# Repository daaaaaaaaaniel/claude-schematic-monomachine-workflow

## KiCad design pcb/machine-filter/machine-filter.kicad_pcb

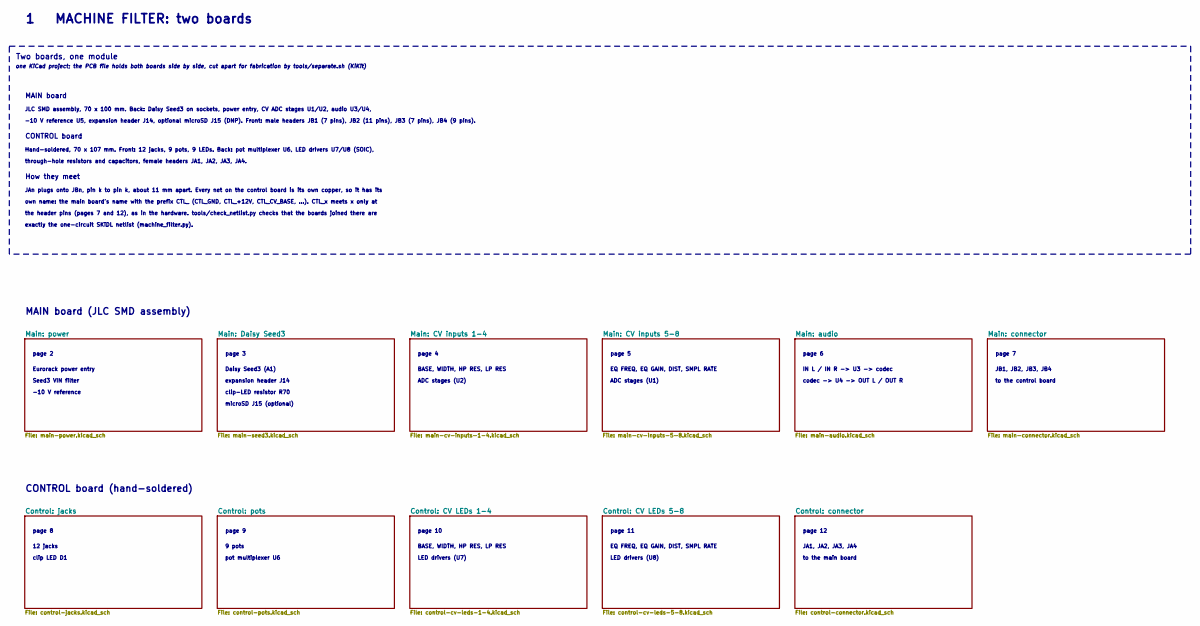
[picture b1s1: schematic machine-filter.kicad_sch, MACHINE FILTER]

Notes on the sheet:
Two boards, one module
one KiCad project; the PCB file holds both boards side by side, cut apart for fabrication by tools/separate.sh (KiKit)
MAIN board
JLC SMD assembly, 70 x 100 mm. Back: Daisy Seed3 on sockets, power entry, CV ADC stages U1/U2, audio U3/U4,
-10 V reference U5, expansion header J14, optional microSD J15 (DNP). Front: male headers JB1 (7 pins), JB2 (11 pins), JB3 (7 pins), JB4 (9 pins).
CONTROL board
Hand-soldered, 70 x 107 mm. Front: 12 jacks, 9 pots, 9 LEDs. Back: pot multiplexer U6, LED drivers U7/U8 (SOIC),
through-hole resistors and capacitors, female headers JA1, JA2, JA3, JA4.
How they meet
JAn plugs onto JBn, pin k to pin k, about 11 mm apart. Every net on the control board is its own copper, so it has its
own name: the main board's name with the prefix CTL_ (CTL_GND, CTL_+12V, CTL_CV_BASE, ...). CTL_x meets x only at
the header pins (pages 7 and 12), as in the hardware. tools/check_netlist.py checks that the boards joined there are
exactly the one-circuit SKiDL netlist (machine_filter.py).
MAIN board (JLC SMD assembly)
page 2
Eurorack power entry
Seed3 VIN filter
-10 V reference
page 3
Daisy Seed3 (A1)
expansion header J14
clip-LED resistor R70
microSD J15 (optional)
page 4
BASE, WIDTH, HP RES, LP RES
ADC stages (U2)
page 5
EQ FREQ, EQ GAIN, DIST, SMPL RATE
ADC stages (U1)
page 6
IN L / IN R -> U3 -> codec
codec -> U4 -> OUT L / OUT R
page 7
JB1, JB2, JB3, JB4
to the control board
CONTROL board (hand-soldered)
page 8
12 jacks
clip LED D1
page 9

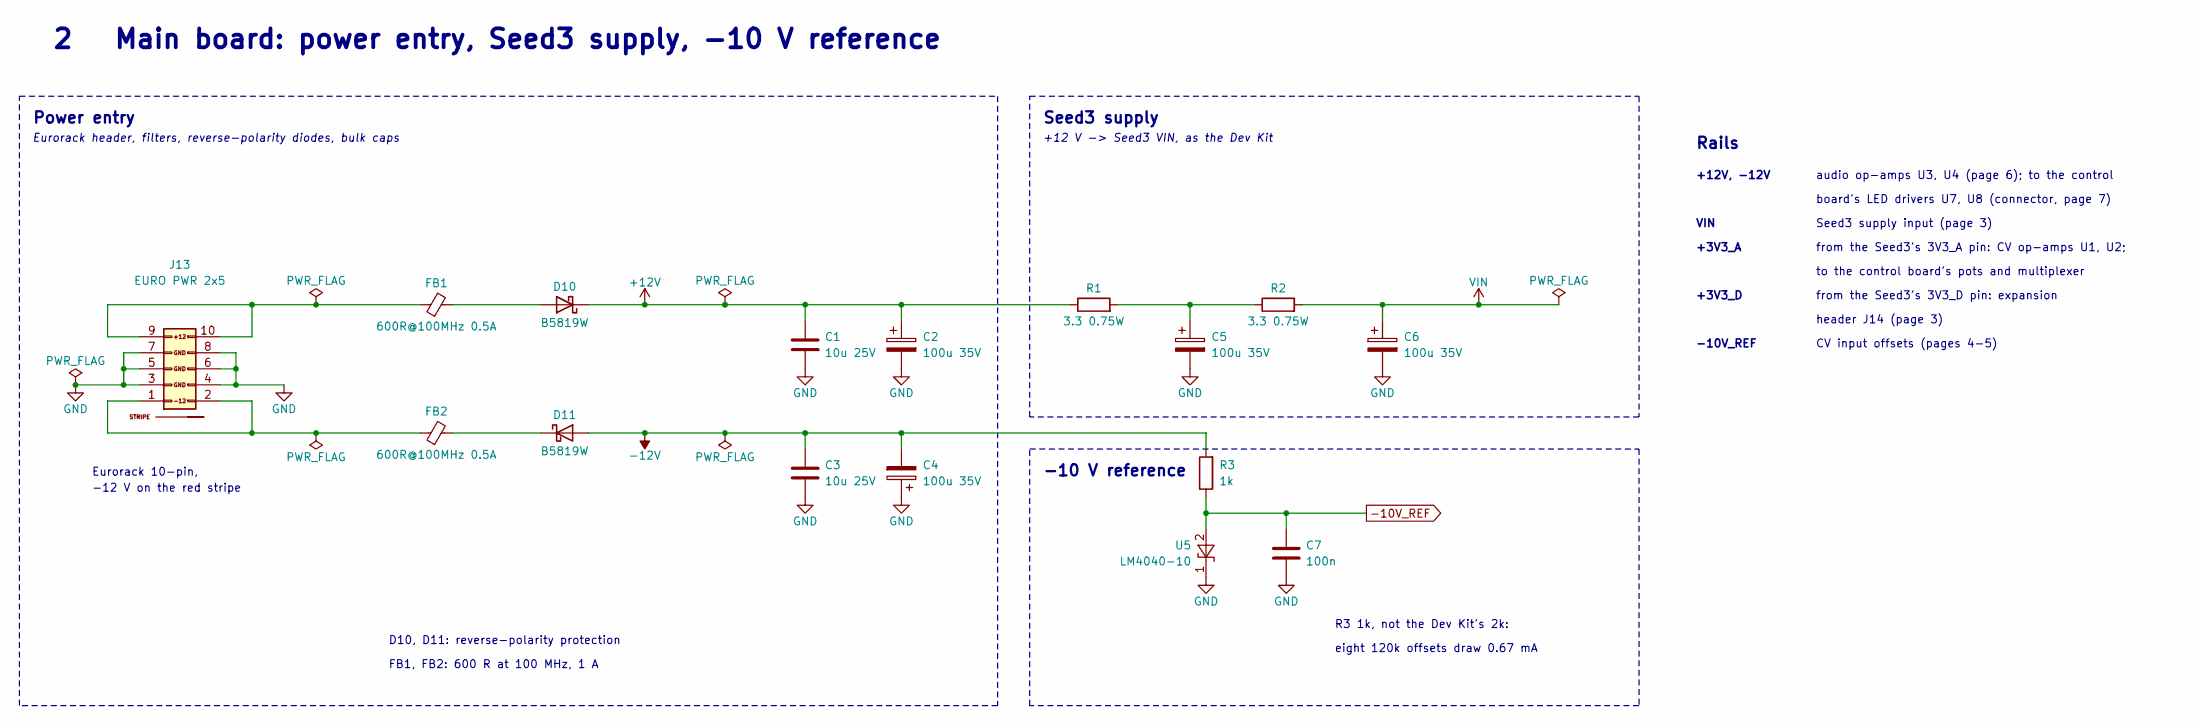
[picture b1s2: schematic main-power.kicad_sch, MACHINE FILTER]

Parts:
C1, C3: 10u 25V; C_0805; MPN CL21A106KAYNNNE; LCSC C15850
C2, C4, C5, C6: 100u 35V; CP_Elec_6.3x7.7; MPN RVT1V101M0607; LCSC C72478
C7: 100n; C_0603; MPN CC0603KRX7R9BB104; LCSC C14663
D10, D11: B5819W; D_SOD-123; MPN B5819W SL; LCSC C8598
FB1, FB2: 600R@100MHz 0.5A; R_0805_2012Metric; MPN GZ2012D601TF; LCSC C1017
J13: EURO PWR 2x5; Pins_2x05_2.54mm_TH_EurorackPower_Shrouded; MPN 2x5 2.54 mm shrouded box header
R1, R2: 3.3 0.75W; R_1206_3216Metric; MPN SG73P2BTTD3R30F; LCSC C2577888
R3: 1k; R_0603; MPN 0603WAF1001T5E; LCSC C21190
U5: LM4040-10; SOT-23; MPN LM4040C10IDBZR; LCSC C201738

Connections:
+12V: C1.1, C2.1, D10.1 (K), R1.1; also elsewhere on the board
-10V_REF: C7.1, R3.1, U5.2 (A); also elsewhere on the board
-12V: C3.2, C4.2, D11.2 (A), R3.2; also elsewhere on the board
GND: C1.2, C2.2, C3.1, C4.1, C5.2, C6.2, C7.2, J13.3 (GND), J13.4 (GND), J13.5 (GND), J13.6 (GND), J13.7 (GND), J13.8 (GND), U5.1 (K); also elsewhere on the board
unnamed: C5.1, R1.2, R2.1
unnamed: D10.2 (A), FB1.2
unnamed: D11.1 (K), FB2.2
unnamed: FB1.1, J13.9 (+12V), J13.10 (+12V)
unnamed: FB2.1, J13.1 (-12V), J13.2 (-12V)
VIN: C6.1, R2.2; also elsewhere on the board

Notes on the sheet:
Power entry
Eurorack header, filters, reverse-polarity diodes, bulk caps
Eurorack 10-pin,
-12 V on the red stripe
Seed3 supply
+12 V -> Seed3 VIN, as the Dev Kit
D10, D11: reverse-polarity protection
FB1, FB2: 600 R at 100 MHz, 1 A
-10 V reference
R3 1k, not the Dev Kit's 2k:
eight 120k offsets draw 0.67 mA
Rails
+12V, -12V
audio op-amps U3, U4 (page 6); to the control
board's LED drivers U7, U8 (connector, page 7)
VIN
Seed3 supply input (page 3)
+3V3_A
from the Seed3's 3V3_A pin: CV op-amps U1, U2;
to the control board's pots and multiplexer
+3V3_D
from the Seed3's 3V3_D pin: expansion
header J14 (page 3)
-10V_REF
CV input offsets (pages 4-5)
2 Main board: power entry, Seed3 supply, -10 V reference

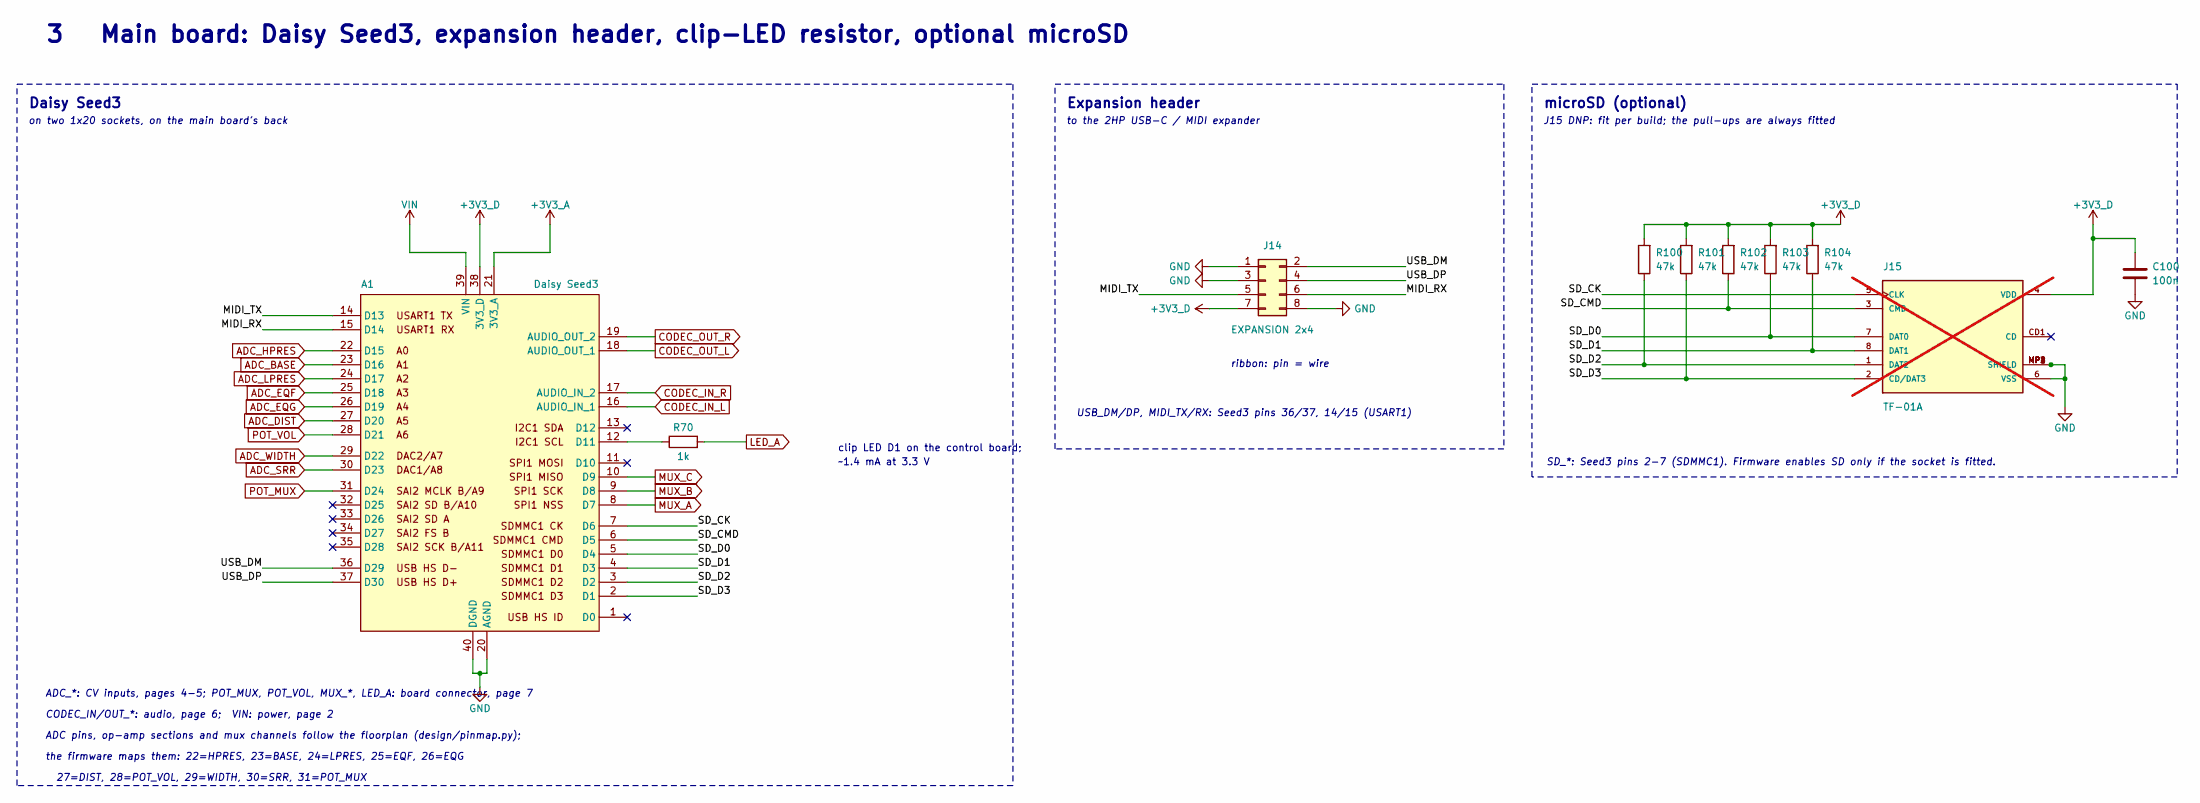
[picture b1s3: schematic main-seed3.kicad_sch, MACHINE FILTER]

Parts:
A1: Daisy Seed3; Daisy_Seed_ES_Sockets; MPN Electrosmith Daisy Seed3 on 2x 1x20 2.5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
C100: 100n; C_0603; MPN CC0603KRX7R9BB104; LCSC C14663
J14: EXPANSION 2x4; Pins_2x04_2.54mm_TH; MPN 2x4 2.54 mm pin header, unshrouded (d)
J15: TF-01A; MPN HRO TF-01A microSD socket, push-push (o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; LCSC C91145; not fitted
R70: 1k; R_0603; MPN 0603WAF1001T5E; LCSC C21190
R100, R101, R102, R103, R104: 47k; R_0603; MPN 0603WAF4702T5E; LCSC C25819

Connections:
+3V3_A: A1.21 (3V3_A); also elsewhere on the board
+3V3_D: A1.38 (3V3_D), C100.1, J14.7, J15.4 (VDD), R100.2, R101.2, R102.2, R103.2, R104.2
/Main: Daisy Seed3/MIDI_RX: A1.15 (D14), J14.6
/Main: Daisy Seed3/MIDI_TX: A1.14 (D13), J14.5
/Main: Daisy Seed3/SD_CK: A1.7 (D6), J15.5 (CLK)
/Main: Daisy Seed3/SD_CMD: A1.6 (D5), J15.3 (CMD), R102.1
/Main: Daisy Seed3/SD_D0: A1.5 (D4), J15.7 (DAT0), R103.1
/Main: Daisy Seed3/SD_D1: A1.4 (D3), J15.8 (DAT1), R104.1
/Main: Daisy Seed3/SD_D2: A1.3 (D2), J15.1 (DAT2), R100.1
/Main: Daisy Seed3/SD_D3: A1.2 (D1), J15.2 (CD/DAT3), R101.1
/Main: Daisy Seed3/USB_DM: A1.36 (D29), J14.2
/Main: Daisy Seed3/USB_DP: A1.37 (D30), J14.4
ADC_BASE: A1.23 (D16); also elsewhere on the board
ADC_DIST: A1.27 (D20); also elsewhere on the board
ADC_EQF: A1.25 (D18); also elsewhere on the board
ADC_EQG: A1.26 (D19); also elsewhere on the board
ADC_HPRES: A1.22 (D15); also elsewhere on the board
ADC_LPRES: A1.24 (D17); also elsewhere on the board
ADC_SRR: A1.30 (D23); also elsewhere on the board
ADC_WIDTH: A1.29 (D22); also elsewhere on the board
CODEC_IN_L: A1.16 (AUDIO_IN_1); also elsewhere on the board
CODEC_IN_R: A1.17 (AUDIO_IN_2); also elsewhere on the board
CODEC_OUT_L: A1.18 (AUDIO_OUT_1); also elsewhere on the board
CODEC_OUT_R: A1.19 (AUDIO_OUT_2); also elsewhere on the board
GND: A1.20 (AGND), A1.40 (DGND), C100.2, J14.1, J14.3, J14.8, J15.6 (VSS), J15.MP1 (SHIELD), J15.MP2 (SHIELD), J15.MP3 (SHIELD), J15.MP4 (SHIELD); also elsewhere on the board
LED_A: R70.2; also elsewhere on the board
MUX_A: A1.8 (D7); also elsewhere on the board
MUX_B: A1.9 (D8); also elsewhere on the board
MUX_C: A1.10 (D9); also elsewhere on the board
unnamed: A1.12 (D11), R70.1
POT_MUX: A1.31 (D24); also elsewhere on the board
POT_VOL: A1.28 (D21); also elsewhere on the board
VIN: A1.39 (VIN); also elsewhere on the board

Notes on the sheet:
Daisy Seed3
on two 1x20 sockets, on the main board's back
clip LED D1 on the control board;
~1.4 mA at 3.3 V
ADC_*: CV inputs, pages 4-5; POT_MUX, POT_VOL, MUX_*, LED_A: board connector, page 7
CODEC_IN/OUT_*: audio, page 6; VIN: power, page 2
ADC pins, op-amp sections and mux channels follow the floorplan (design/pinmap.py);
the firmware maps them: 22=HPRES, 23=BASE, 24=LPRES, 25=EQF, 26=EQG
27=DIST, 28=POT_VOL, 29=WIDTH, 30=SRR, 31=POT_MUX
Expansion header
to the 2HP USB-C / MIDI expander
ribbon: pin = wire
USB_DM/DP, MIDI_TX/RX: Seed3 pins 36/37, 14/15 (USART1)
microSD (optional)
J15 DNP: fit per build; the pull-ups are always fitted
SD_*: Seed3 pins 2-7 (SDMMC1). Firmware enables SD only if the socket is fitted.
3 Main board: Daisy Seed3, expansion header, clip-LED resistor, optional microSD

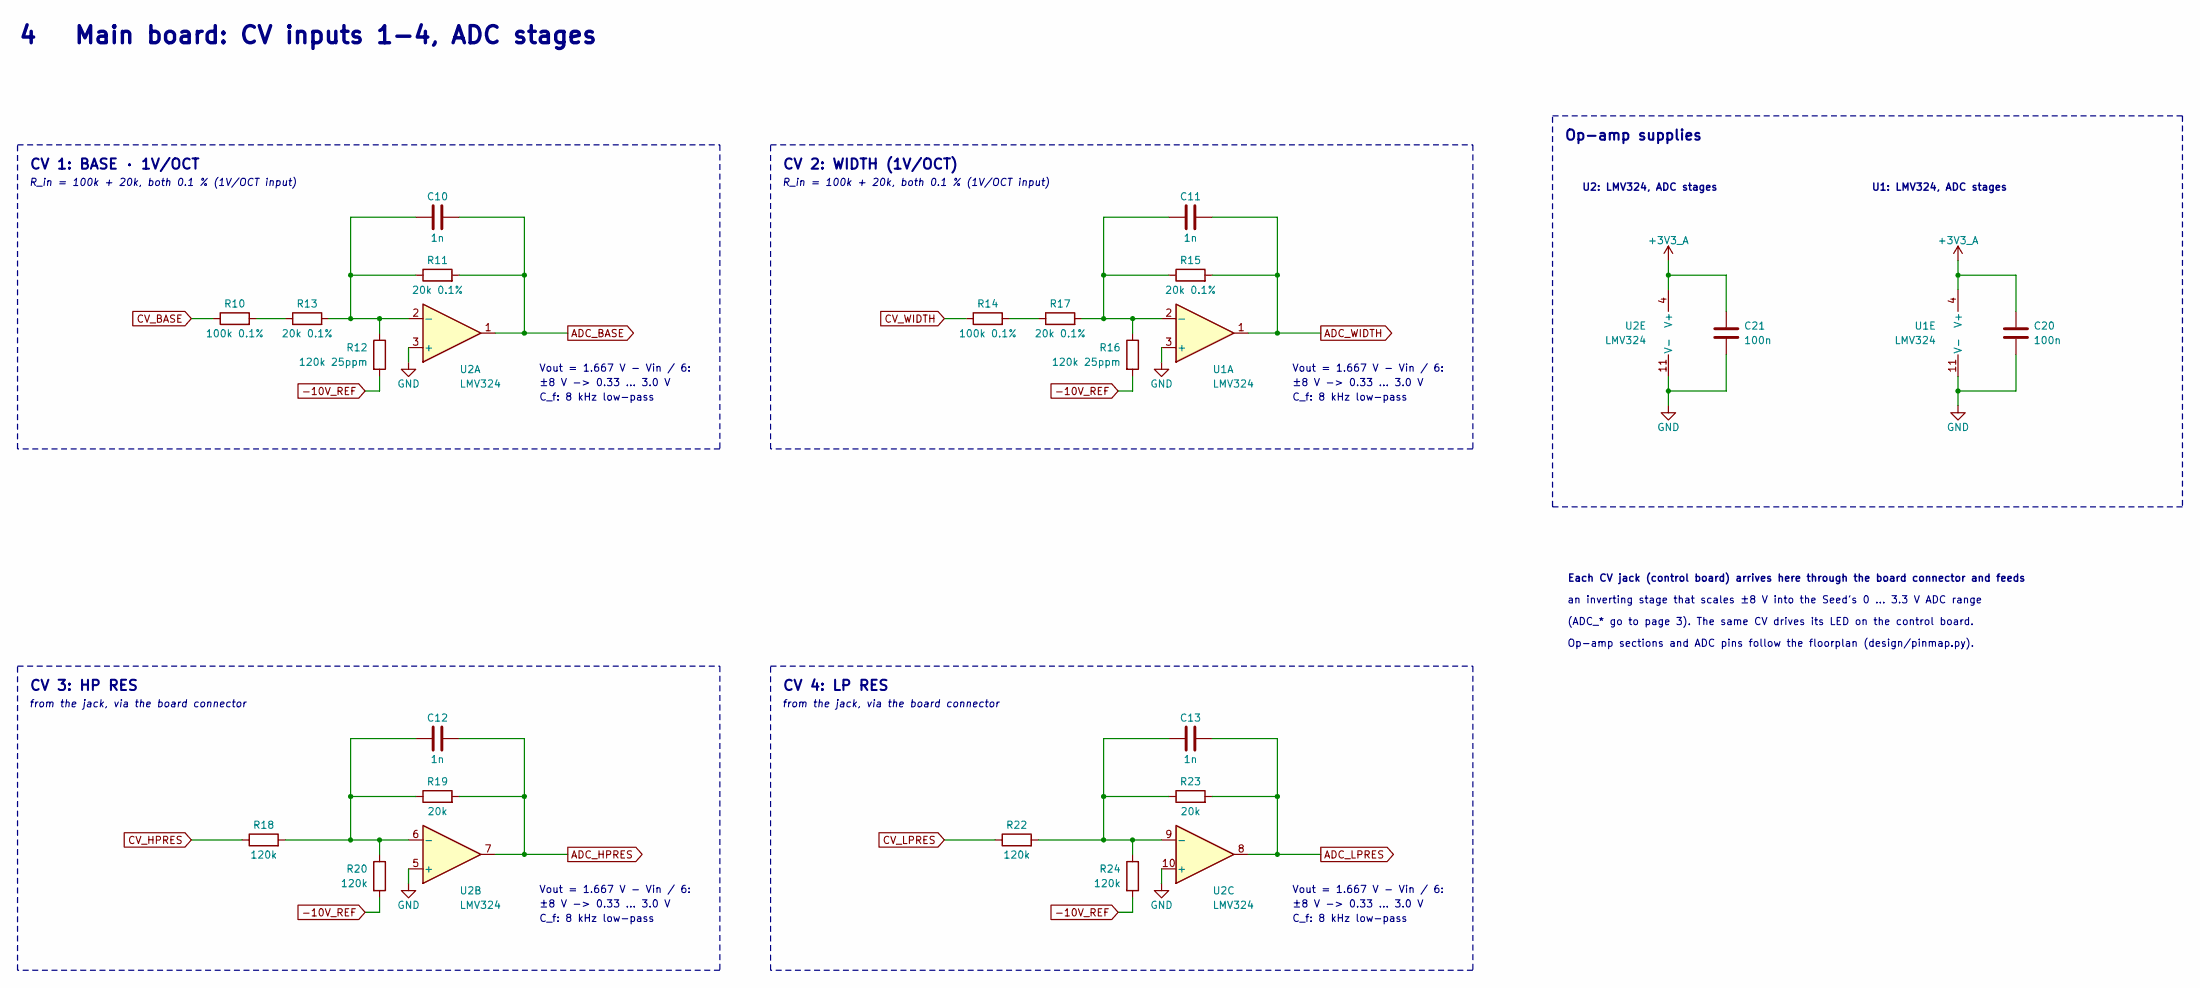
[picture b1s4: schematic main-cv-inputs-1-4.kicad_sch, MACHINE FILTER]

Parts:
C10, C11, C12, C13: 1n; C_0603; MPN CL10B102KB8NNNC; LCSC C1588
C20, C21: 100n; C_0603; MPN CC0603KRX7R9BB104; LCSC C14663
R10, R14: 100k 0.1%; R_0603; MPN RT0603BRD07100KL; LCSC C122538
R11, R13, R15, R17: 20k 0.1%; R_0603; MPN RT0603BRD0720KL; LCSC C723637
R12, R16: 120k 25ppm; R_0603; MPN RT0603DRD07120KL; LCSC C862537
R18, R20, R22, R24: 120k; R_0603; MPN 0603WAF1203T5E; LCSC C25808
R19, R23: 20k; R_0603; MPN 0603WAF2002T5E; LCSC C4184
U1, U2: LMV324; SOIC-14_3.9x8.65mm_Pitch1.27mm; MPN LMV324IDR; LCSC C7974

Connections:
+3V3_A: C20.1, C21.1, U1.4 (V+), U2.4 (V+); also elsewhere on the board
-10V_REF: R12.2, R16.2, R20.2, R24.2; also elsewhere on the board
ADC_BASE: C10.2, R11.2, U2.1; also elsewhere on the board
ADC_HPRES: C12.2, R19.2, U2.7; also elsewhere on the board
ADC_LPRES: C13.2, R23.2, U2.8; also elsewhere on the board
ADC_WIDTH: C11.2, R15.2, U1.1; also elsewhere on the board
CV_BASE: R10.1; also elsewhere on the board
CV_HPRES: R18.1; also elsewhere on the board
CV_LPRES: R22.1; also elsewhere on the board
CV_WIDTH: R14.1; also elsewhere on the board
GND: C20.2, C21.2, U1.3 (+), U1.11 (V-), U2.3 (+), U2.5 (+), U2.10 (+), U2.11 (V-); also elsewhere on the board
unnamed: R10.2, R13.1
unnamed: R14.2, R17.1
unnamed: C11.1, R15.1, R16.1, R17.2, U1.2 (-)
unnamed: C10.1, R11.1, R12.1, R13.2, U2.2 (-)
unnamed: C12.1, R18.2, R19.1, R20.1, U2.6 (-)
unnamed: C13.1, R22.2, R23.1, R24.1, U2.9 (-)

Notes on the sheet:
CV 1: BASE · 1V/OCT
R_in = 100k + 20k, both 0.1 % (1V/OCT input)
Vout = 1.667 V - Vin / 6:
±8 V -> 0.33 ... 3.0 V
C_f: 8 kHz low-pass
CV 2: WIDTH (1V/OCT)
CV 3: HP RES
from the jack, via the board connector
CV 4: LP RES
Op-amp supplies
U2: LMV324, ADC stages
U1: LMV324, ADC stages
Each CV jack (control board) arrives here through the board connector and feeds
an inverting stage that scales ±8 V into the Seed's 0 ... 3.3 V ADC range
(ADC_* go to page 3). The same CV drives its LED on the control board.
Op-amp sections and ADC pins follow the floorplan (design/pinmap.py).
4 Main board: CV inputs 1-4, ADC stages

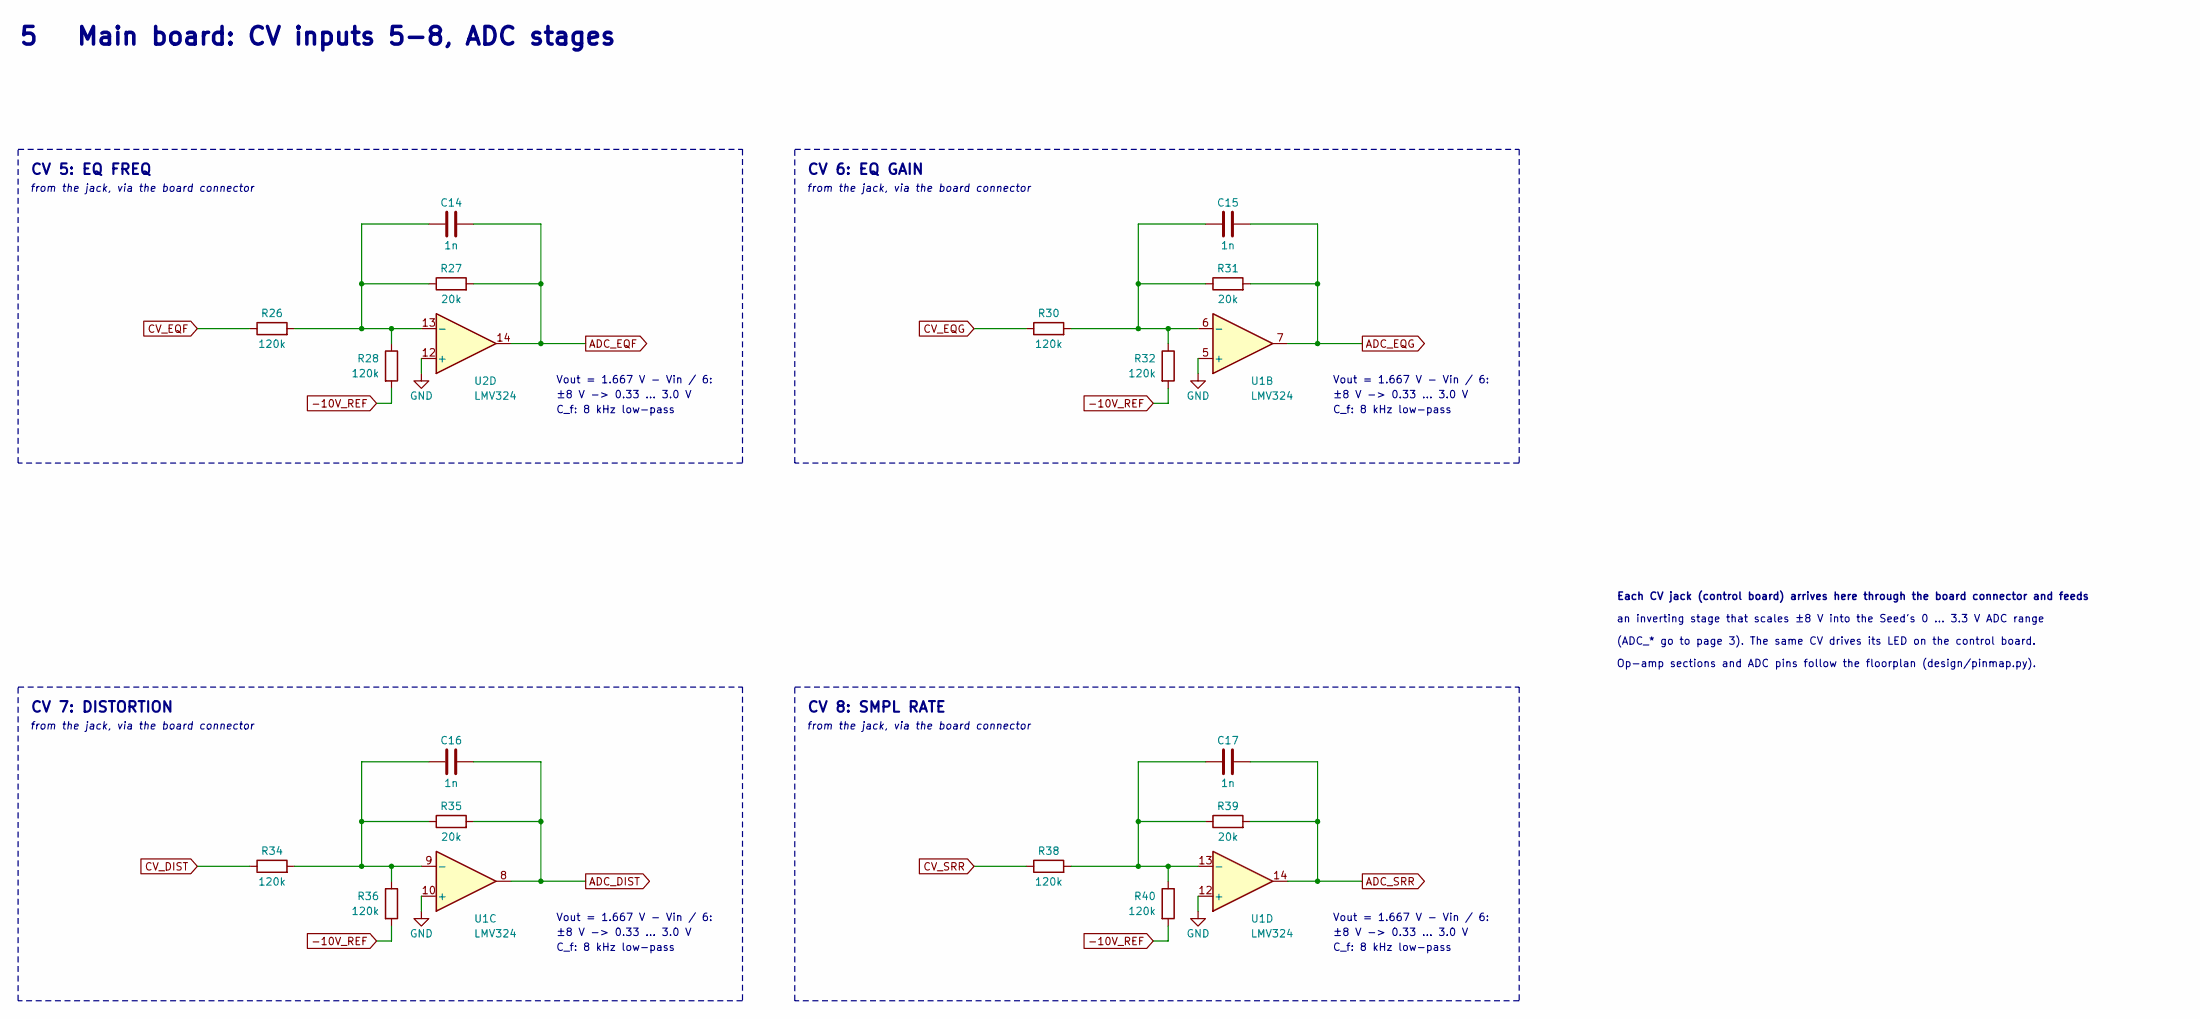
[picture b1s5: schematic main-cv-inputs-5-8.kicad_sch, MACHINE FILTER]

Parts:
C14, C15, C16, C17: 1n; C_0603; MPN CL10B102KB8NNNC; LCSC C1588
R26, R28, R30, R32, R34, R36, R38, R40: 120k; R_0603; MPN 0603WAF1203T5E; LCSC C25808
R27, R31, R35, R39: 20k; R_0603; MPN 0603WAF2002T5E; LCSC C4184
U1, U2: LMV324; SOIC-14_3.9x8.65mm_Pitch1.27mm; MPN LMV324IDR; LCSC C7974

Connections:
-10V_REF: R28.2, R32.2, R36.2, R40.2; also elsewhere on the board
ADC_DIST: C16.2, R35.2, U1.8; also elsewhere on the board
ADC_EQF: C14.2, R27.2, U2.14; also elsewhere on the board
ADC_EQG: C15.2, R31.2, U1.7; also elsewhere on the board
ADC_SRR: C17.2, R39.2, U1.14; also elsewhere on the board
CV_DIST: R34.1; also elsewhere on the board
CV_EQF: R26.1; also elsewhere on the board
CV_EQG: R30.1; also elsewhere on the board
CV_SRR: R38.1; also elsewhere on the board
GND: U1.5 (+), U1.10 (+), U1.12 (+), U2.12 (+); also elsewhere on the board
unnamed: C15.1, R30.2, R31.1, R32.1, U1.6 (-)
unnamed: C16.1, R34.2, R35.1, R36.1, U1.9 (-)
unnamed: C17.1, R38.2, R39.1, R40.1, U1.13 (-)
unnamed: C14.1, R26.2, R27.1, R28.1, U2.13 (-)

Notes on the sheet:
CV 5: EQ FREQ
from the jack, via the board connector
Vout = 1.667 V - Vin / 6:
±8 V -> 0.33 ... 3.0 V
C_f: 8 kHz low-pass
CV 6: EQ GAIN
CV 7: DISTORTION
CV 8: SMPL RATE
Each CV jack (control board) arrives here through the board connector and feeds
an inverting stage that scales ±8 V into the Seed's 0 ... 3.3 V ADC range
(ADC_* go to page 3). The same CV drives its LED on the control board.
Op-amp sections and ADC pins follow the floorplan (design/pinmap.py).
5 Main board: CV inputs 5-8, ADC stages

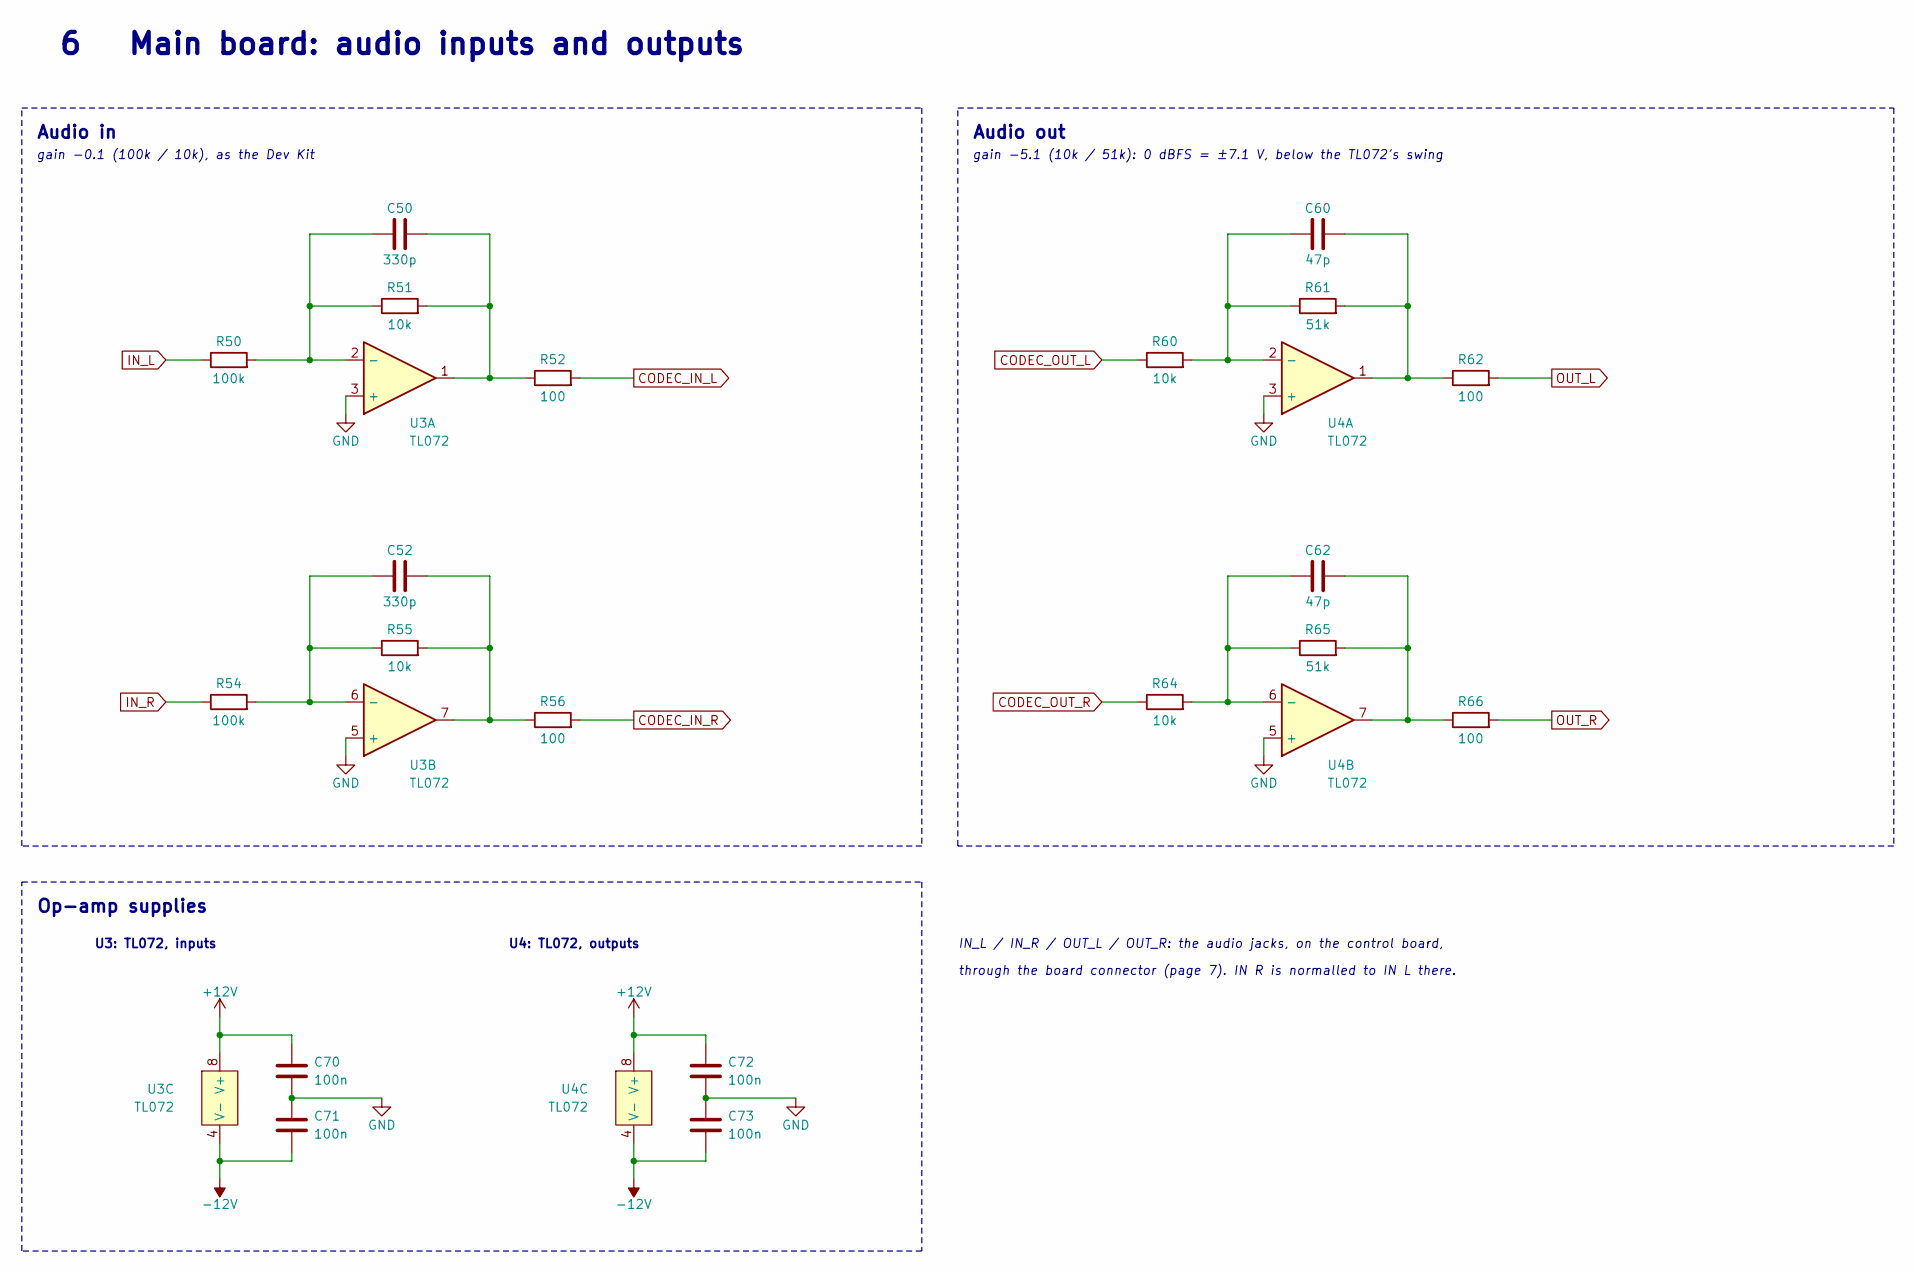
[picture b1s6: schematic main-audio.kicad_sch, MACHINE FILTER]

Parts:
C50, C52: 330p; C_0603; MPN CL10C331JB8NNNC; LCSC C1664
C60, C62: 47p; C_0603; MPN CL10C470JB8NNNC; LCSC C1671
C70, C71, C72, C73: 100n; C_0603; MPN CC0603KRX7R9BB104; LCSC C14663
R50, R54: 100k; R_0603; MPN 0603WAF1003T5E; LCSC C25803
R51, R55, R60, R64: 10k; R_0603; MPN 0603WAF1002T5E; LCSC C25804
R52, R56, R62, R66: 100; R_0603; MPN 0603WAF1000T5E; LCSC C22775
R61, R65: 51k; R_0603; MPN 0603WAF5102T5E; LCSC C23196
U3, U4: TL072; SOIC-8_3.9x4.9mm_Pitch1.27mm; MPN TL072CDT; LCSC C6961

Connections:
+12V: C70.1, C72.1, U3.8 (V+), U4.8 (V+); also elsewhere on the board
-12V: C71.2, C73.2, U3.4 (V-), U4.4 (V-); also elsewhere on the board
CODEC_IN_L: R52.2; also elsewhere on the board
CODEC_IN_R: R56.2; also elsewhere on the board
CODEC_OUT_L: R60.1; also elsewhere on the board
CODEC_OUT_R: R64.1; also elsewhere on the board
GND: C70.2, C71.1, C72.2, C73.1, U3.3 (+), U3.5 (+), U4.3 (+), U4.5 (+); also elsewhere on the board
IN_L: R50.1; also elsewhere on the board
IN_R: R54.1; also elsewhere on the board
unnamed: C50.2, R51.2, R52.1, U3.1
unnamed: C52.2, R55.2, R56.1, U3.7
unnamed: C60.2, R61.2, R62.1, U4.1
unnamed: C62.2, R65.2, R66.1, U4.7
unnamed: C50.1, R50.2, R51.1, U3.2 (-)
unnamed: C52.1, R54.2, R55.1, U3.6 (-)
unnamed: C60.1, R60.2, R61.1, U4.2 (-)
unnamed: C62.1, R64.2, R65.1, U4.6 (-)
OUT_L: R62.2; also elsewhere on the board
OUT_R: R66.2; also elsewhere on the board

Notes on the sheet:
Audio in
gain -0.1 (100k / 10k), as the Dev Kit
Audio out
gain -5.1 (10k / 51k): 0 dBFS = ±7.1 V, below the TL072's swing
Op-amp supplies
U3: TL072, inputs
U4: TL072, outputs
IN_L / IN_R / OUT_L / OUT_R: the audio jacks, on the control board,
through the board connector (page 7). IN R is normalled to IN L there.
6 Main board: audio inputs and outputs

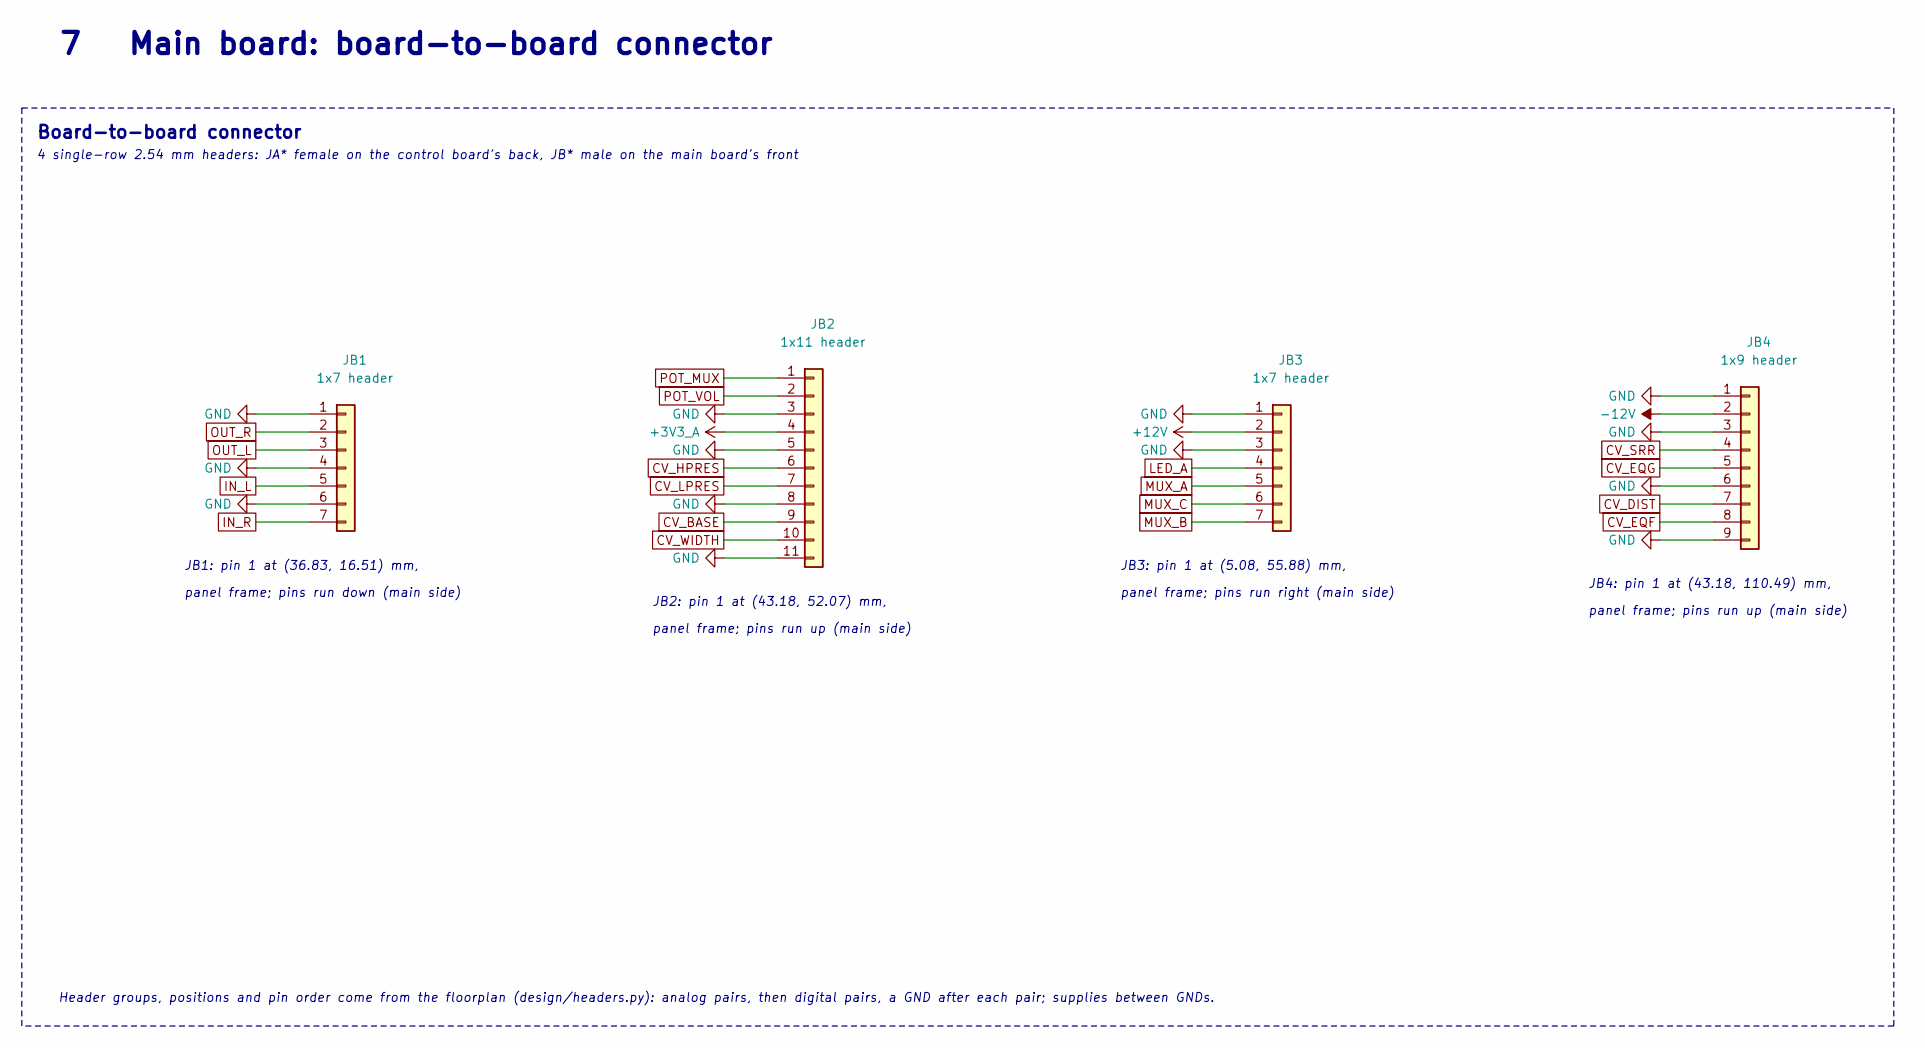
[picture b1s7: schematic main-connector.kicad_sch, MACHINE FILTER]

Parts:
JB1, JB3: 1x7 header; PinHeader_1x07_P2.54mm_Vertical; MPN 2.54 mm male pin header 1x7
JB2: 1x11 header; PinHeader_1x11_P2.54mm_Vertical; MPN 2.54 mm male pin header 1x11
JB4: 1x9 header; PinHeader_1x09_P2.54mm_Vertical; MPN 2.54 mm male pin header 1x9

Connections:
+3V3_A: JB2.4; also elsewhere on the board
+12V: JB3.2; also elsewhere on the board
-12V: JB4.2; also elsewhere on the board
CV_BASE: JB2.9; also elsewhere on the board
CV_DIST: JB4.7; also elsewhere on the board
CV_EQF: JB4.8; also elsewhere on the board
CV_EQG: JB4.5; also elsewhere on the board
CV_HPRES: JB2.6; also elsewhere on the board
CV_LPRES: JB2.7; also elsewhere on the board
CV_SRR: JB4.4; also elsewhere on the board
CV_WIDTH: JB2.10; also elsewhere on the board
GND: JB1.1, JB1.4, JB1.6, JB2.3, JB2.5, JB2.8, JB2.11, JB3.1, JB3.3, JB4.1, JB4.3, JB4.6, JB4.9; also elsewhere on the board
IN_L: JB1.5; also elsewhere on the board
IN_R: JB1.7; also elsewhere on the board
LED_A: JB3.4; also elsewhere on the board
MUX_A: JB3.5; also elsewhere on the board
MUX_B: JB3.7; also elsewhere on the board
MUX_C: JB3.6; also elsewhere on the board
OUT_L: JB1.3; also elsewhere on the board
OUT_R: JB1.2; also elsewhere on the board
POT_MUX: JB2.1; also elsewhere on the board
POT_VOL: JB2.2; also elsewhere on the board

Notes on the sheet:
Board-to-board connector
4 single-row 2.54 mm headers: JA* female on the control board's back, JB* male on the main board's front
JB1: pin 1 at (36.83, 16.51) mm,
panel frame; pins run down (main side)
JB2: pin 1 at (43.18, 52.07) mm,
panel frame; pins run up (main side)
JB3: pin 1 at (5.08, 55.88) mm,
panel frame; pins run right (main side)
JB4: pin 1 at (43.18, 110.49) mm,
Header groups, positions and pin order come from the floorplan (design/headers.py): analog pairs, then digital pairs, a GND after each pair; supplies between GNDs.
7 Main board: board-to-board connector
